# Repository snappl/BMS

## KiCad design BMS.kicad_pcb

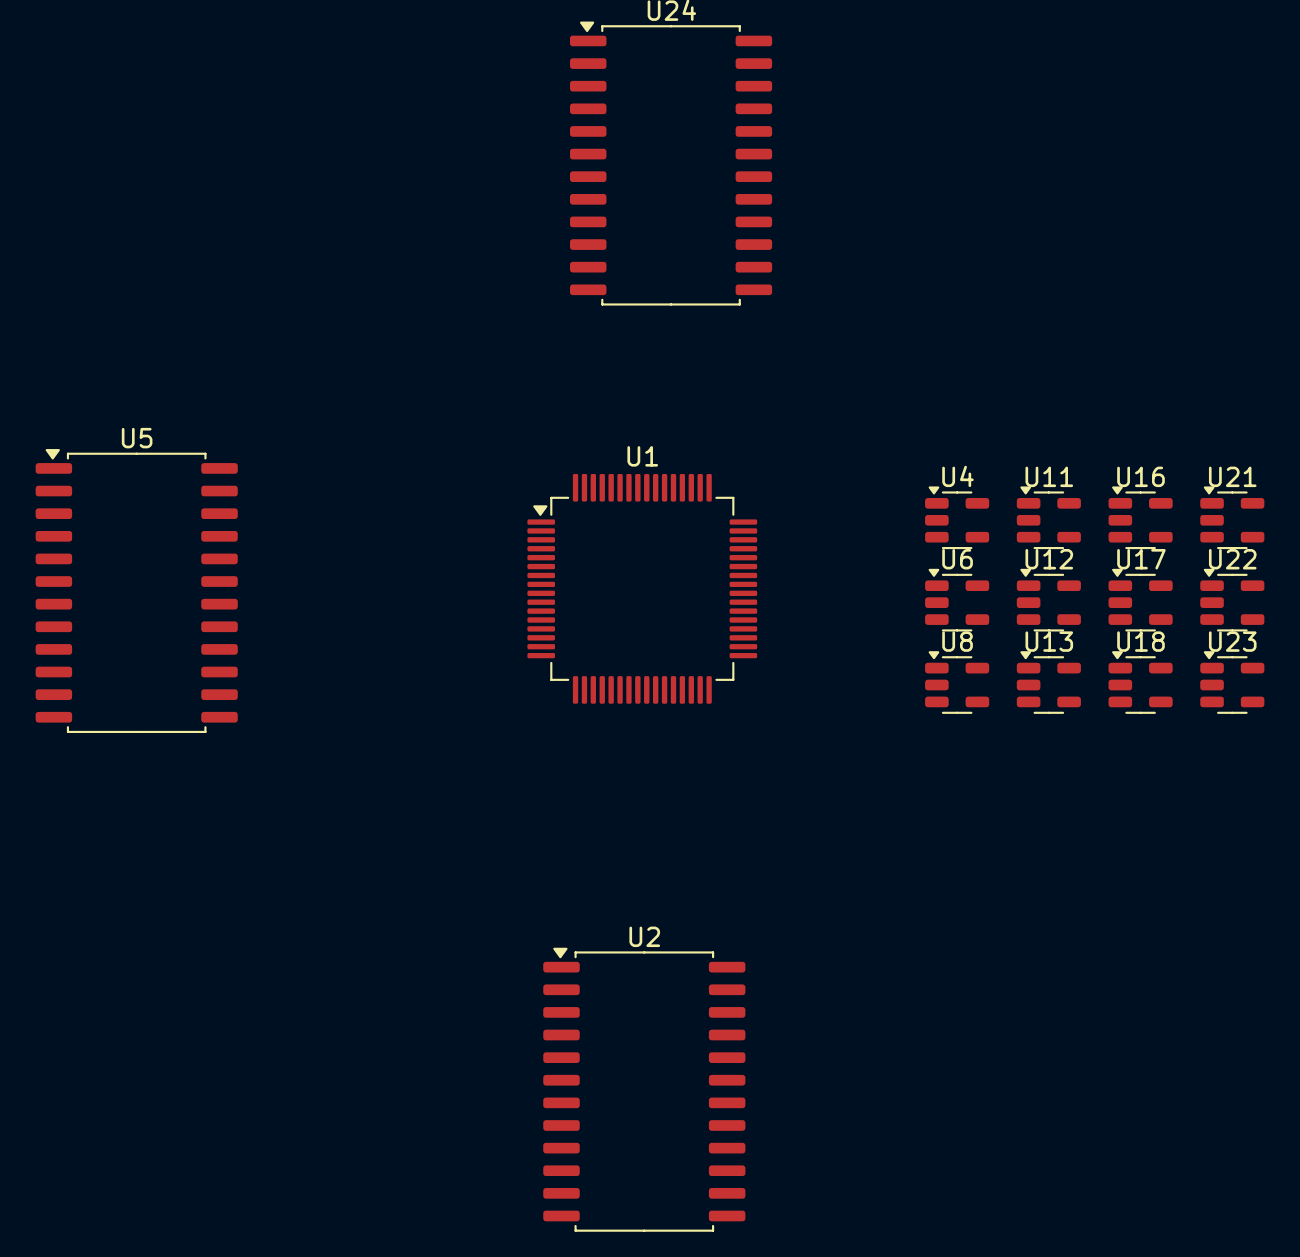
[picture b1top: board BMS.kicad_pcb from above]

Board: 2 copper layers, 16 parts (0 on the bottom side), 14 nets, no tracks yet.

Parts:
U1: STM32F446RETx; LQFP-64_10x10mm_P0.5mm
U2, U5, U24: CD74HC4067M; SOIC-24W_7.5x15.4mm_P1.27mm
U4, U6, U8, U11, U12, U13, U16, U17, U18, U21, U22, U23: OP179GRT; SOT-23-5

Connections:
+3.3V: U1.19 (VDD), U1.32 (VDD), U1.48 (VDD), U1.64 (VDD), U2.24 (VCC), U5.24 (VCC), U24.24 (VCC)
+5V: U4.2 (V+), U6.2 (V+), U8.2 (V+), U11.2 (V+), U12.2 (V+), U13.2 (V+), U16.2 (V+), U17.2 (V+), U18.2 (V+), U21.2 (V+), U22.2 (V+), U23.2 (V+)
Batt-temp12: U1.12 (VSSA), U1.18 (VSS), U1.31 (VSS), U1.47 (VSS), U1.63 (VSS), U2.12 (GND), U4.5 (V-), U5.2 (I7), U5.5 (I4), U5.7 (I2), U5.12 (GND), U5.21 (I10), U6.5 (V-), U8.5 (V-), U11.5 (V-), U12.5 (V-), U13.5 (V-), U16.5 (V-), U17.5 (V-), U18.5 (V-), U21.5 (V-), U22.5 (V-), U23.5 (V-), U24.12 (GND)
OA-select0: U1.37 (PC6), U2.10 (S0)
OA-select1: U1.38 (PC7), U2.11 (S1)
OA-select2: U1.39 (PC8), U2.14 (S2)
OA-select3: U1.40 (PC9), U2.13 (S3)
TS_select0: U1.59 (PB7), U5.10 (S0)
TS_select1: U1.58 (PB6), U5.11 (S1)
TS_select2: U1.57 (PB5), U5.14 (S2)
TS_select3: U1.61 (PB8), U5.13 (S3)
mux1ADC: U1.20 (PA4), U5.1 (COM)
mux3ADC: U1.22 (PA6), U24.1 (COM)
muxADC2: U1.21 (PA5), U2.1 (COM)
